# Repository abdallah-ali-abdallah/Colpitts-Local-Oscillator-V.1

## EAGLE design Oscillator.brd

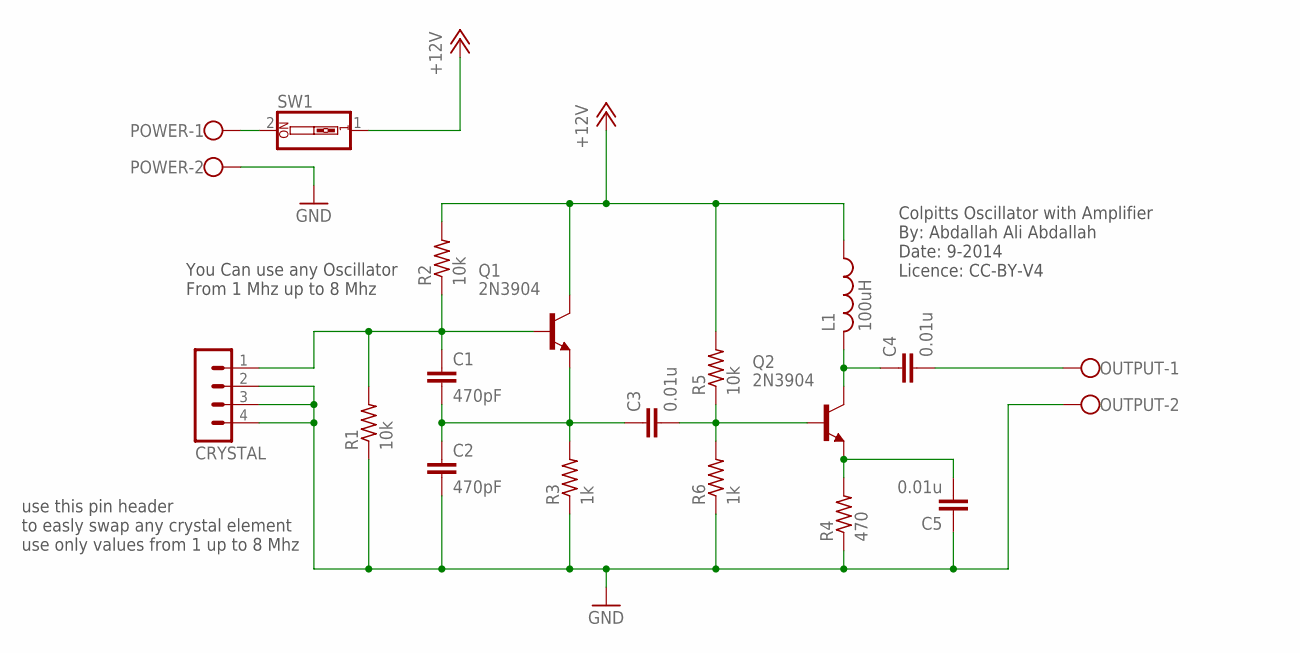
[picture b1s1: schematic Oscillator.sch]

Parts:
C1, C2: 470pF; C025-025X050
C3, C4, C5: 0.01u; C025-025X050
CRYSTAL: MA04-1
L1: 100uH; 0204/7
OUTPUT: W237-102
POWER: W237-102
Q1, Q2: 2N3904; TO92
R1, R2, R5: 10k; 0204/7
R3, R6: 1k; 0204/7
R4: 470; 0204/7
SW1: SW_DIP-1; EDG-01

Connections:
+12V: L1.1, Q1.1 (C), R2.2, R5.2, SW1.1
GND: C2.2, C5.1, CRYSTAL.2, CRYSTAL.3, CRYSTAL.4, OUTPUT.2, POWER.2, R1.1, R3.1, R4.1, R6.1
unnamed: C1.1, CRYSTAL.1, Q1.2 (B), R1.2, R2.1
unnamed: C1.2, C2.1, C3.1, Q1.3 (E), R3.2
unnamed: C3.2, Q2.2 (B), R5.1, R6.2
unnamed: C5.2, Q2.3 (E), R4.2
unnamed: C4.1, L1.2, Q2.1 (C)
unnamed: C4.2, OUTPUT.1
unnamed: POWER.1, SW1.2

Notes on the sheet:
You Can use any Oscillator From 1 Mhz up to 8 Mhz
Colpitts Oscillator with Amplifier By: Abdallah Ali Abdallah Date: 9-2014 Licence: CC-BY-V4
use this pin header to easly swap any crystal element use only values from 1 up to 8 Mhz

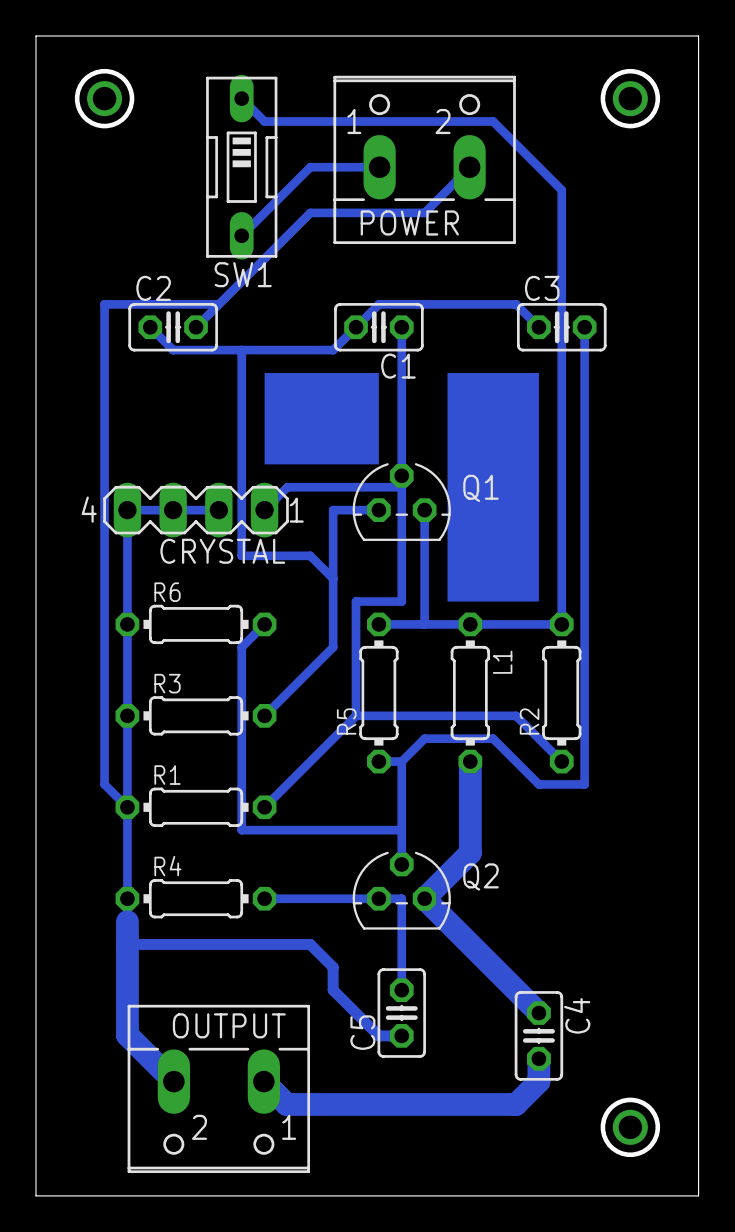
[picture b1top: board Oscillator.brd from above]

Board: 2 copper layers, 36.8 x 64.4 mm, 18 parts (0 on the bottom side), 9 nets.

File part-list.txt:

Partlist

Exported from Oscillator.sch at 12/09/2014 05:13:13 ã

EAGLE Version 6.3.0 Copyright (c) 1988-2012 CadSoft

Assembly variant: 

Part     Value          Device          Package      Library        Sheet

C1       470pF          C-EU025-025X050 C025-025X050 rcl            1
C2       470pF          C-EU025-025X050 C025-025X050 rcl            1
C3       0.01u          C-EU025-025X050 C025-025X050 rcl            1
C4       0.01u          C-EU025-025X050 C025-025X050 rcl            1
C5       0.01u          C-EU025-025X050 C025-025X050 rcl            1
CRYSTAL                 MA04-1          MA04-1       con-lstb       1
L1       100uH          L-US0204/7      0204/7       rcl            1
OUTPUT                  W237-102        W237-102     con-wago-500   1
POWER                   W237-102        W237-102     con-wago-500   1
Q1       2N3904         2N3904          TO92         transistor-npn 1
Q2       2N3904         2N3904          TO92         transistor-npn 1
R1       10k            R-US_0204/7     0204/7       rcl            1
R2       10k            R-US_0204/7     0204/7       rcl            1
R3       1k             R-US_0204/7     0204/7       rcl            1
R4       470            R-US_0204/7     0204/7       rcl            1
R5       10k            R-US_0204/7     0204/7       rcl            1
R6       1k             R-US_0204/7     0204/7       rcl            1
SW1                     SW_DIP-1        EDG-01       special        1

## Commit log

2014-09-14 :tada: Added .gitattributes & .gitignore files
2014-09-14 Colpitts Oscillator Circuit
    This circuit work as a local oscillator, you can use any crystal
    oscillator from 1 up to 8 Mhz
